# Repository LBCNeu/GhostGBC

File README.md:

# GhostGBC

Simple GBC emulator project in portable C++ for custom hardware (e.g. ESP32) by lbcn.eu.

## Contact:

* info@lbcn.eu
* https://lbcn.eu

## Credits:

* **Blargg (Shay Green)** - [Game Boy Hardware Test ROMs](https://github.com/retrio/gb-test-roms)

# References used:

## Videos
### Ultimate GB Talk
https://youtu.be/HyzD8pNlpwI

## Technical Info
https://gekkio.fi/files/gb-docs/gbctr.pdf

## Info on Opcodes
https://izik1.github.io/gbops/
https://meganesu.github.io/generate-gb-opcodes/
https://pastraiser.com/cpu/gameboy/gameboy_opcodes.html
https://blog.ollien.com/posts/gb-daa/

## Pan Docs
https://gbdev.io/pandocs
https://gbdev.io/pandocs/Specifications.html
https://gbdev.io/pandocs/Power_Up_Sequence.html

## Z80 / Intel 8080 info
https://z80-heaven.wikidot.com/

# Hardware:

## William Durand's KiCad Libraries
https://github.com/willdurand/kicad-libs

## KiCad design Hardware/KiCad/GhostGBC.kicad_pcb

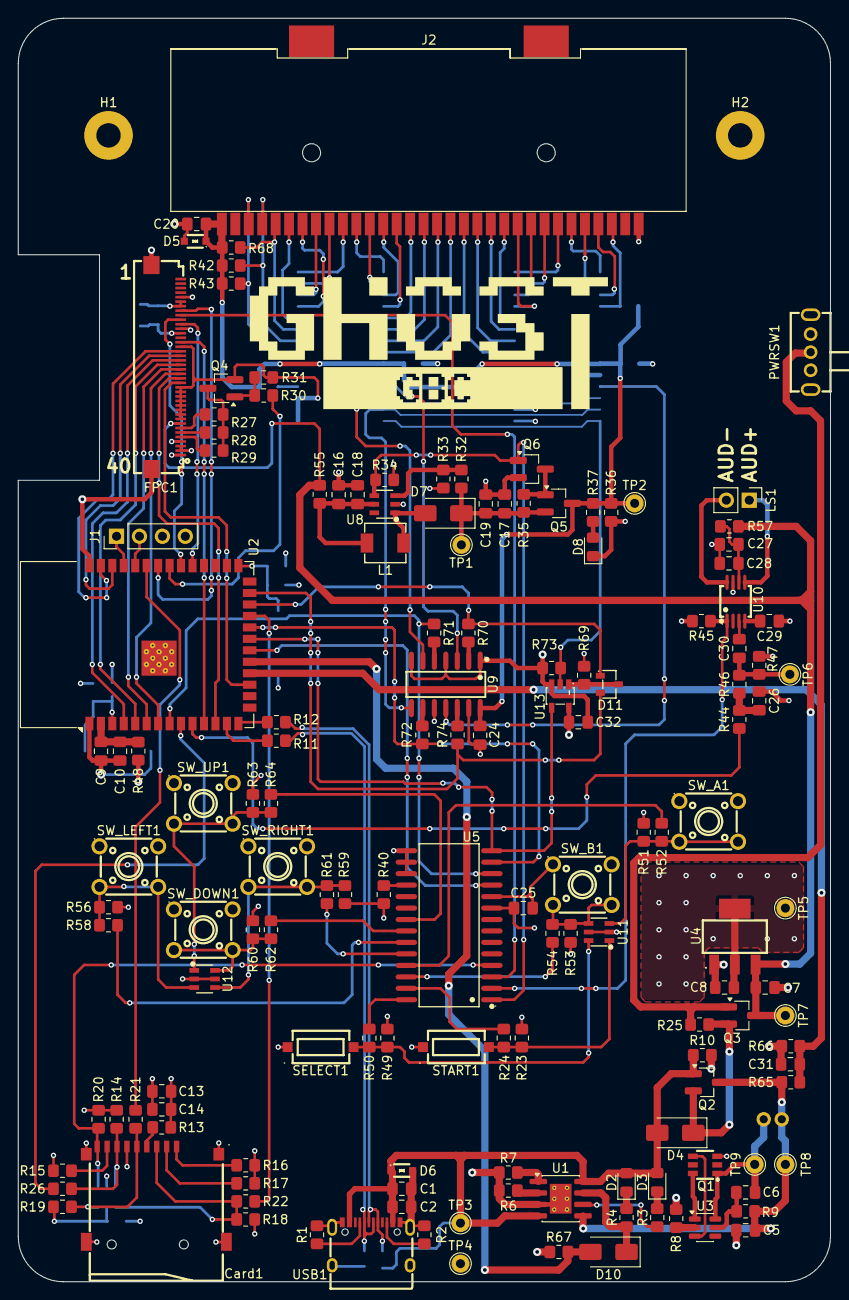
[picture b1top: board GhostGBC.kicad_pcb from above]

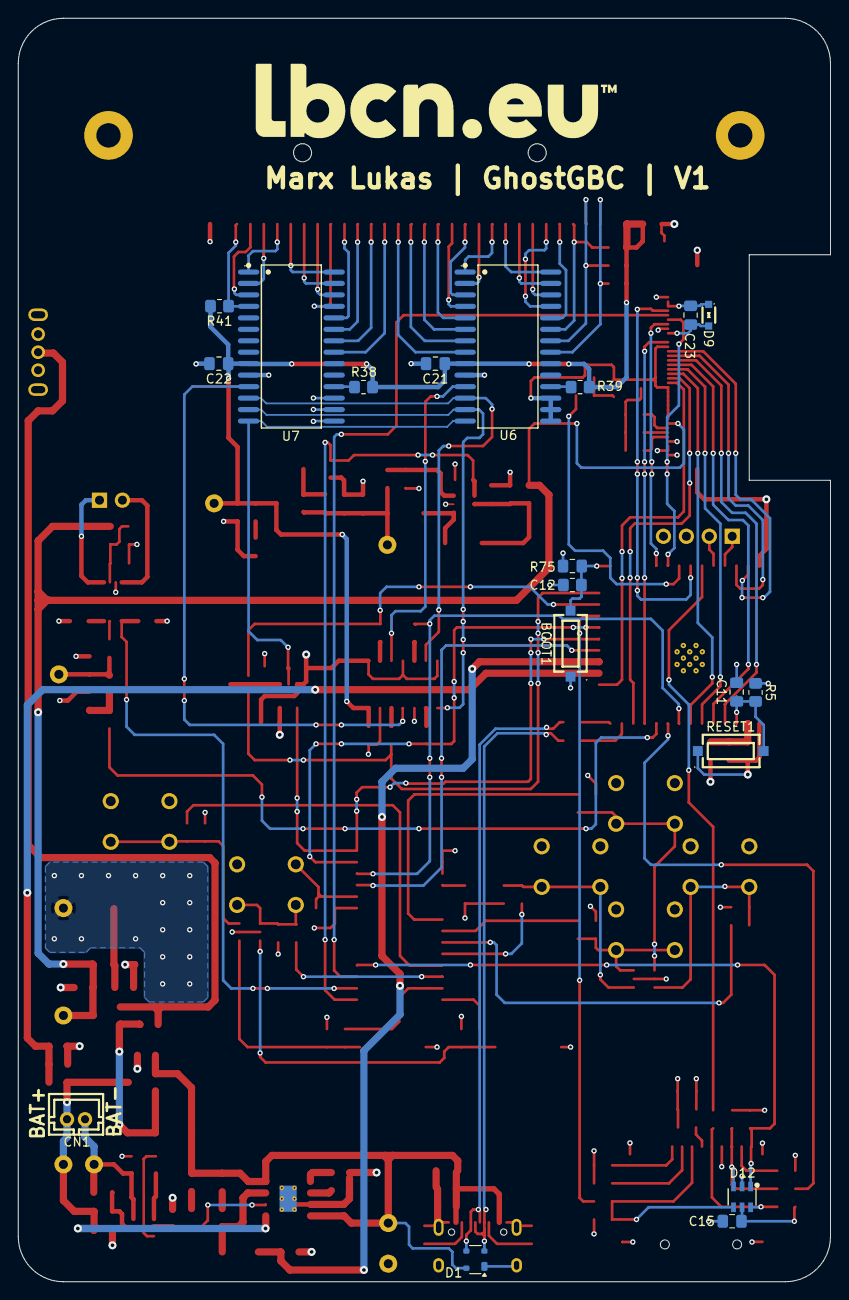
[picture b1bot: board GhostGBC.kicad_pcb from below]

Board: 4 copper layers, 90.0 x 140.0 mm, 166 parts (19 on the bottom side), 141 nets.

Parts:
BOOT1: HX TS-1101-C-W; C36498960_SW-SMD_HX-TS-1101-C-W
C1, C5: 10µF; C_0805_2012Metric_Pad1.18x1.45mm_HandSolder
C2, C6, C9, C14, C15, C18, C19, C20, C21, C22, C23, C24, C25, C29, C30, C31, C32: 100nF; C_0805_2012Metric_Pad1.18x1.45mm_HandSolder
C7, C8: 4.7uF; C_0805_2012Metric_Pad1.18x1.45mm_HandSolder
C10, C13, C27: 10uF; C_0805_2012Metric_Pad1.18x1.45mm_HandSolder
C11, C12, C28: 1uF; C_0805_2012Metric_Pad1.18x1.45mm_HandSolder
C16, C17: 22µF; C_0805_2012Metric_Pad1.18x1.45mm_HandSolder
C26: 10nF; C_0805_2012Metric_Pad1.18x1.45mm_HandSolder
CN1: B2B-PH-K-S(LF)(SN); C131337_CONN-TH_B2B-PH-K-S
Card1: TF-01A; C91145_TF-SMD_TF-01A
D1: PRTR5V0U2X; SOT-143
D2, D3, D8: LED; LED_0805_2012Metric_Pad1.15x1.40mm_HandSolder
D4, D7, D10: SS34; D_SMA
D5, D6: PESD5V0S1BA; C19224_SOD-323_L1_7-W1_3-LS2_5-BI
D9: PESD3V3S1BA; C7472904_SOD-323_L1_7-W1_3-LS2_5-BI
D11: BAT54A_C727124; C727124_SOT-23-3_L2_9-W1_3-P1_90-LS2_4-BR
D12: USBLC6-4SC6; C111212_SOT-23-6_L2_9-W1_6-P0_95-LS2_8-BL
FPC1: FPC-05FB-40PH20; C2856837_FPC-SMD_40P-P0_50_XUNPU_FPC-05FB-40PH20
H1, H2: MountingHole_Pad_MP; MountingHole_2.7mm_M2.5_Pad
J1: Conn_01x04; PinHeader_1x04_P2.54mm_Vertical
J2: GB_GBC_1x32
L1: FXL0420-4R7-M; C167208_IND-SMD_L4_4-W4_2
LS1: Speaker; PinHeader_1x02_P2.54mm_Vertical
PWRSW1: SK12D07VG4; C393937_SW-TH_SK12D07VG4
Q1: FS8205A_C2830320; C2830320_SOT-23-6_L2_9-W1_6-P0_95-LS2_8-BR
Q2, Q3, Q5: AO3401A; SOT-23_Handsoldering
Q4, Q6: AO3400A; SOT-23_Handsoldering
R1, R2: 5.1k; R_0805_2012Metric_Pad1.20x1.40mm_HandSolder
R3, R4, R8, R24, R37, R44, R50, R52, R54, R58, R61, R62, R64, R70, R71, R72, R74: 1k; R_0805_2012Metric_Pad1.20x1.40mm_HandSolder
R5, R7, R14, R15, R16, R17, R18, R19, R20, R23, R31, R36, R38, R39, R40, R41, R42, R43, R45, R46, R49, R51, R53, R56, R59, R60, R63, R67, R68, R69, R73, R75: 10k; R_0805_2012Metric_Pad1.20x1.40mm_HandSolder
R6: 3k; R_0805_2012Metric_Pad1.20x1.40mm_HandSolder
R9, R30: 100Ω; R_0805_2012Metric_Pad1.20x1.40mm_HandSolder
R10, R25, R34, R35, R65, R66: 100k; R_0805_2012Metric_Pad1.20x1.40mm_HandSolder
R11, R12: 22Ω; R_0805_2012Metric_Pad1.20x1.40mm_HandSolder
R13, R21, R22, R26, R48, R55, R57: 0Ω; R_0805_2012Metric_Pad1.20x1.40mm_HandSolder
R27, R28, R29: 82Ω; R_0805_2012Metric_Pad1.20x1.40mm_HandSolder
R32: 110k; R_0805_2012Metric_Pad1.20x1.40mm_HandSolder
R33: 15k; R_0805_2012Metric_Pad1.20x1.40mm_HandSolder
R47: 2k; R_0805_2012Metric_Pad1.20x1.40mm_HandSolder
RESET1: HX TS-1101-C-W; C36498960_SW-SMD_HX-TS-1101-C-W
SELECT1: HX TS-1101-C-W; C36498960_SW-SMD_HX-TS-1101-C-W
START1: HX TS-1101-C-W; C36498960_SW-SMD_HX-TS-1101-C-W
SW_A1: B3F-1000; C93157_KEY-TH_4P-L6_2-W6_2-P4_50-LS6_5
SW_B1: B3F-1000; C93157_KEY-TH_4P-L6_2-W6_2-P4_50-LS6_5
SW_DOWN1: B3F-1000; C93157_KEY-TH_4P-L6_2-W6_2-P4_50-LS6_5
SW_LEFT1: B3F-1000; C93157_KEY-TH_4P-L6_2-W6_2-P4_50-LS6_5
SW_RIGHT1: B3F-1000; C93157_KEY-TH_4P-L6_2-W6_2-P4_50-LS6_5
SW_UP1: B3F-1000; C93157_KEY-TH_4P-L6_2-W6_2-P4_50-LS6_5
TP1, TP2, TP3, TP4, TP5, TP6, TP7, TP8, TP9: TestPoint; TestPoint_THTPad_D2.0mm_Drill1.0mm
U1: TP4056-42-ESOP8; SOIC-8-1EP_3.9x4.9mm_P1.27mm_EP2.41x3.3mm_ThermalVias
U2: ESP32-S3-WROOM-1-N16R8; ESP32-S3-WROOM-1
U3: DW01A; SOT-23-6
U4: AP2114H-3.3TRG1; C150716_SOT-223_L6_7-W3_5-P2_30-BR
U5, U6, U7: MCP23S17T-E/SO; C144293_SOIC-28_L17_9-W7_5-P1_27-LS10_3-BL
U8: MT3608; C84817_SOT-23-6_L2_9-W1_6-P0_95-LS2_8-BL
U9: SN74AHCT125DR; C155176_SOIC-14_L8_7-W3_9-P1_27-LS6_0-BL
U10: PAM8302AASCR; C113367_MSOP-8_L3_0-W3_0-P0_65-LS5_0-BL
U11, U12: PESD3V3S4UD; C5126000_SOT-23-6_L2_9-W1_6-P0_95-LS2_8-BL
U13: 74LVC1G125GV_C52140413; C52140413_SOT-23-5_L3_0-W1_7-P0_95-LS2_8-BR
USB1: TYPE-C 16PIN 2MD(073); C2765186_USB-C-SMD_TYPE-C-16PIN-2MD-073

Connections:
5V_EN: Q6.1 (G), R34.1, U5.1 (GPB0), U8.4 (EN)
+3V3: C8.1, C13.1, C14.1, C15.1, C23.1, C25.1, C32.1, D9.1 (C), D12.5, FPC1.6, FPC1.7, FPC1.12, FPC1.38, FPC1.39, J1.3, R5.1, R13.2, R14.1, R15.1, R16.1, R17.1, R18.1, R19.1, R20.1, R23.1, R40.1, R48.1, R49.1, R51.1, R53.1, R56.1, R59.1, R60.1, R63.1, R67.1, R69.1, R75.1, TP5.1 (1_1), U4.2 (VOUT), U4.4 (VOUT), U5.9 (VDD), U13.5 (Vcc)
+5V: C20.1, C21.1, C22.1, C24.1, D5.1, J2.1 (VCC), Q5.3 (D), R36.1, R37.1, R38.1, R39.1, R41.2, R42.1, R43.1, R68.1, TP2.1 (1_1), U6.9 (VDD), U7.9 (VDD), U9.14 (VCC)
AUD+: LS1.1, U10.5 (VO+)
AUD-: LS1.2, U10.8 (VO-)
AUD_EN: R45.1, U5.2 (GPB1), U10.1 (SD#)
BAT+: C5.1, CN1.2, Q2.3 (D), R9.2, R65.1, TP8.1 (1_1), U1.5 (BAT)
BAT-: C6.2, CN1.1, Q1.1 (S1), TP9.1 (1_1), U3.6 (GND)
BAT_ADC: C31.1, R65.2, R66.1, U2.18 (IO10)
BAT_CHRG: D10.2 (A), R67.2, U2.19 (IO11)
BTN_A: R52.2, U5.25 (GPA4)
BTN_B: R54.2, U5.26 (GPA5)
BTN_DOWN: R62.2, U5.22 (GPA1)
BTN_LEFT: R58.2, U5.23 (GPA2)
BTN_RIGHT: R61.2, U5.24 (GPA3)
BTN_SELECT: R50.2, U5.28 (GPA7)
BTN_START: R24.2, U5.27 (GPA6)
BTN_UP: R64.2, U5.21 (GPA0)
CS_U5: U2.20 (IO12), U5.11 (CS#)
CS_U6: D11.1 (A), R70.1, U2.24 (IO47)
CS_U6_5V: U6.11 (CS#), U9.3 (1Y)
CS_U7: D11.2 (A), R74.1, U2.25 (IO48)
CS_U7_5V: U7.11 (CS#), U9.11 (4Y)
D+: D1.3 (I/O2), R12.2, USB1.A6 (Dp1), USB1.B6 (Dp2)
D-: D1.2 (I/O1), R11.2, USB1.A7 (Dn1), USB1.B7 (Dn2)
GND: BOOT1.1, C1.2, C2.2, C5.2, C7.2, C8.2, C9.2, C10.2, C11.2, C12.2, C13.2, C14.2, C15.2, C16.2, C17.2, C18.2, C19.2, C20.2, C21.2, C22.2, C23.2, C24.2, C25.2, C26.2, C27.2, C28.2, C29.1, C31.2, C32.2, Card1.6 (VSS), Card1.10 (GND), Card1.11 (GND), Card1.12 (GND), Card1.13 (GND), D1.1 (GND), D5.2, D6.2, D8.1 (K), D9.2 (A), D12.2, FPC1.5, FPC1.13, FPC1.16, FPC1.25, FPC1.26, FPC1.27, FPC1.28, FPC1.29, FPC1.30, FPC1.31, FPC1.32, FPC1.37, FPC1.40, FPC1.41, FPC1.42, J1.4, J2.32 (GND), PWRSW1.3, PWRSW1.4, PWRSW1.5, Q1.3 (S2), Q4.2 (S), Q6.2 (S), R1.2, R2.2, R6.2, R7.2, R8.2, R10.2, R31.2, R33.2, R34.2, R36.2, R45.2, R47.2, R66.2, R73.2, RESET1.1, SELECT1.1, START1.1, SW_A1.1, SW_A1.2, SW_B1.1, SW_B1.2, SW_DOWN1.1, SW_DOWN1.2, SW_LEFT1.1, SW_LEFT1.2, SW_RIGHT1.1, SW_RIGHT1.2, SW_UP1.1, SW_UP1.2, TP4.1 (1_1), U1.3 (GND), U1.9 (EPAD), U2.1 (GND), U2.40 (GND), U2.41 (GND), U4.1 (GND), U5.10 (VSS), U5.15 (A0), U5.16 (A1), U5.17 (A2), U6.10 (VSS), U6.15 (A0), U6.16 (A1), U6.17 (A2), U7.10 (VSS), U7.15 (A0), U7.16 (A1), U7.17 (A2), U8.2 (GND), U9.1 (1OE#), U9.4 (2OE#), U9.7 (GND), U9.10 (3OE#), U9.13 (4OE#), U10.7 (GND), U11.2, U11.5, U12.2, U12.5, U13.3 (GND), USB1.13 (EH), USB1.14 (EH), USB1.A1B12 (GND), USB1.B1A12 (GND)
LCD_BL: R30.1, U2.33 (IO40)
LCD_CS: FPC1.9, U5.3 (GPB2)
LCD_DB0: FPC1.17, U2.39 (IO1)
LCD_DB1: FPC1.18, U2.38 (IO2)
LCD_DB2: FPC1.19, U2.4 (IO4)
LCD_DB3: FPC1.20, U2.5 (IO5)
LCD_DB4: FPC1.21, U2.6 (IO6)
LCD_DB5: FPC1.22, U2.7 (IO7)
LCD_DB6: FPC1.23, U2.12 (IO8)
LCD_DB7: FPC1.24, U2.17 (IO9)
LCD_FMARK: FPC1.8, U2.34 (IO41)
LCD_RS: FPC1.10, U2.32 (IO39)
LCD_RST_N: FPC1.15, U2.11 (IO18)
LCD_WR: FPC1.11, U2.31 (IO38)
unnamed: C26.1, R44.2, R46.1
unnamed: Card1.2 (CDDAT3(CS)), R17.2
unnamed: Card1.5 (CLK(SCLK)), D12.6, R19.2, R21.2
unnamed: Card1.3 (CMD(DI)), D12.4, R18.2, R22.2
unnamed: Card1.7 (DAT0(D0)), D12.3, R14.2, R26.2
unnamed: Card1.8 (DAT1(RSV)), R15.2
unnamed: Card1.1 (DAT2(RSV)), R16.2
unnamed: Card1.4 (VDD), R13.1
unnamed: D2.1 (K), R4.1
unnamed: D3.1 (K), R3.1
unnamed: D7.2 (A), L1.2, U8.1 (SW)
unnamed: C17.1, C19.1, D7.1 (K), Q5.2 (S), R32.1, R35.1, TP1.1 (1_1)
unnamed: D8.2 (A), R37.2
unnamed: D10.1 (K), R4.2, U1.7 (~CHRG)
unnamed: D11.3 (K), R69.2, U13.1 (OE#)
unnamed: FPC1.34, R27.2
unnamed: FPC1.35, R28.2
unnamed: FPC1.36, R29.2
unnamed: J2.6 (A0), U6.24 (GPA3)
unnamed: J2.7 (A1), U6.25 (GPA4)
unnamed: J2.8 (A2), U6.26 (GPA5)
unnamed: J2.9 (A3), U6.27 (GPA6)
unnamed: J2.10 (A4), U6.28 (GPA7)
unnamed: J2.11 (A5), U6.1 (GPB0)
unnamed: J2.12 (A6), U6.2 (GPB1)
unnamed: J2.13 (A7), U6.3 (GPB2)
unnamed: J2.14 (A8), U6.4 (GPB3)
unnamed: J2.15 (A9), U6.5 (GPB4)
unnamed: J2.16 (A10), U6.6 (GPB5)
unnamed: J2.17 (A11), U6.7 (GPB6)
unnamed: J2.18 (A12), U6.8 (GPB7)
unnamed: J2.19 (A13), U7.21 (GPA0)
unnamed: J2.20 (A14), U7.22 (GPA1)
unnamed: J2.21 (A15), U7.23 (GPA2)
unnamed: J2.22 (D0), U7.24 (GPA3)
unnamed: J2.23 (D1), U7.25 (GPA4)
unnamed: J2.24 (D2), U7.26 (GPA5)
unnamed: J2.25 (D3), U7.27 (GPA6)
unnamed: J2.26 (D4), U7.28 (GPA7)
unnamed: J2.27 (D5), U7.1 (GPB0)
unnamed: J2.28 (D6), U7.2 (GPB1)
unnamed: J2.29 (D7), U7.3 (GPB2)
unnamed: J2.5 (~CS), R68.2, U6.23 (GPA2)
unnamed: J2.4 (~RD), R42.2, U6.22 (GPA1)
unnamed: J2.30 (~RES), R41.1, U7.4 (GPB3)
unnamed: J2.3 (~WR), R43.2, U6.21 (GPA0)
unnamed: Q1.6 (G1), U3.1 (OD)
unnamed: Q1.4 (G2), U3.3 (OC)
unnamed: PWRSW1.2, Q3.1 (G), R25.2
unnamed: Q4.3 (D), R27.1, R28.1, R29.1
unnamed: Q4.1 (G), R30.2, R31.1
unnamed: Q5.1 (G), Q6.3 (D), R35.2
unnamed: R23.2, R24.1, START1.2, U11.1
unnamed: R49.2, R50.1, SELECT1.2, U11.6
unnamed: R51.2, R52.1, SW_A1.3, SW_A1.4, U11.3
unnamed: R53.2, R54.1, SW_B1.3, SW_B1.4, U11.4
unnamed: R56.2, R58.1, SW_LEFT1.3, SW_LEFT1.4, U12.3
unnamed: R59.2, R61.1, SW_RIGHT1.3, SW_RIGHT1.4, U12.4
unnamed: R60.2, R62.1, SW_DOWN1.3, SW_DOWN1.4, U12.6
unnamed: R63.2, R64.1, SW_UP1.3, SW_UP1.4, U12.1
unnamed: R6.1, U1.2 (PROG)
unnamed: R7.1, U1.1 (TEMP)
unnamed: R3.2, U1.6 (~STDBY)
unnamed: C9.1, C10.1, R48.2, U2.2 (3V3)
unnamed: C11.1, R5.2, RESET1.2, U2.3 (EN)
unnamed: BOOT1.2, C12.1, R75.2, U2.27 (IO0)
unnamed: R12.1, U2.14 (USB_D+)
unnamed: R11.1, U2.13 (USB_D-)
unnamed: R8.1, U3.2 (CS)
unnamed: C6.1, R9.1, U3.5 (VCC)
unnamed: R40.2, U5.18 (RESET#)
unnamed: R39.2, U6.18 (RESET#)
unnamed: R38.2, U7.18 (RESET#)
unnamed: R32.2, R33.1, U8.3 (FB)
unnamed: C16.1, C18.1, L1.1, R55.2, U8.5 (IN)
unnamed: R70.2, U9.2 (1A)
unnamed: R71.2, U9.5 (2A)
unnamed: R72.1, U9.9 (3A)
unnamed: R74.2, U9.12 (4A)
unnamed: C30.2, U10.3 (IN+)
unnamed: C29.2, U10.4 (IN-)
unnamed: C27.1, C28.1, R57.2, U10.6 (VDD)
unnamed: R1.1, USB1.A5 (CC1)
unnamed: R2.1, USB1.B5 (CC2)
RC_IN: R44.1, U2.10 (IO17)
RC_OUT: C30.1, R46.2, R47.1, TP6.1 (1_1)
RX: J1.2, U2.36 (RXD0)
SD_CD: Card1.9 (CD), D12.1, R20.2, U5.4 (GPB3)
SD_CLK: R21.1, U2.35 (IO42)
SD_CMD: R22.1, U2.23 (IO21)
SD_DAT: R26.1, U2.9 (IO16)
SPI_MISO: U2.21 (IO13), U5.14 (SO), U13.4 (Y)
SPI_MISO_5V: R73.1, U6.14 (SO), U7.14 (SO), U13.2 (A)
SPI_MOSI: R72.2, U2.22 (IO14), U5.13 (SI)
SPI_MOSI_5V: U6.13 (SI), U7.13 (SI), U9.8 (3Y)
SPI_SCK: R71.1, U2.8 (IO15), U5.12 (SCK)
SPI_SCK_5V: U6.12 (SCK), U7.12 (SCK), U9.6 (2Y)
TX: J1.1, U2.37 (TXD0)
VBUS: C1.1, C2.1, D1.4 (VCC), D2.2 (A), D3.2 (A), D4.2 (A), D6.1, Q2.1 (G), R10.1, TP3.1 (1_1), U1.4 (V_{CC}), U1.8 (CE), USB1.A4B9 (VBUS), USB1.B4A9 (VBUS)
VPWR: C7.1, FPC1.33, Q3.3 (D), R55.1, R57.1, TP7.1 (1_1), U4.3 (VIN)
VSYS: D4.1 (K), Q2.2 (S), Q3.2 (S), R25.1
